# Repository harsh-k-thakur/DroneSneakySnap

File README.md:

# DroneSneakySnap

This project was build as a part of my quarter studies at University of California San Diego.
This project was executed in a group of two. My partner Rye Gleason and I shared the idea and code together to build an end product. 

This project started with understanding dynamics and kinematics of drone. How does Roll, Pitch, Yaw and Throttle works in an open space.

Once I understood the basic dynamics of the drone. 

I started building with the Hardware. For this I used '''Fusion360''' to create new libraries for my IMU, LEDS and Resistors.
Some of the libraries were directly provided to us, and which are readily available in Fusion360 as well. Thus, understanding the basic schematic of a particular part and utilizing the knowledge of that part to integrate in the main project was important. 
You can see datasheet and schmetics of different electronics component under [datasheeet]('/datasheeet/') folder.

All the necessary things related to Hardware are available in [Hardware]('/Hardware/') folder. Things like Schematics, Fusion360 files, Gerber Files are located in the [Hardware]('/Hardware/') folder. Feel free to check those out.

Once done with Hardware, we started working on software. 
While our Printed Circuit Board (PCB) got printed and came back to us we were given a temporary quadcopter in order to start with programming. 
For the software we had Atmega Arduino Micro-controller on the Flight Controller Board. 
Started the project with basic communication between the remote and the quadcopter using Radio Frequency, testing each motors individually works at different spped using Pulse Width Modulation (PWM).
Integrated throttle control from remote and RF together so that we can control the speed using the remote.

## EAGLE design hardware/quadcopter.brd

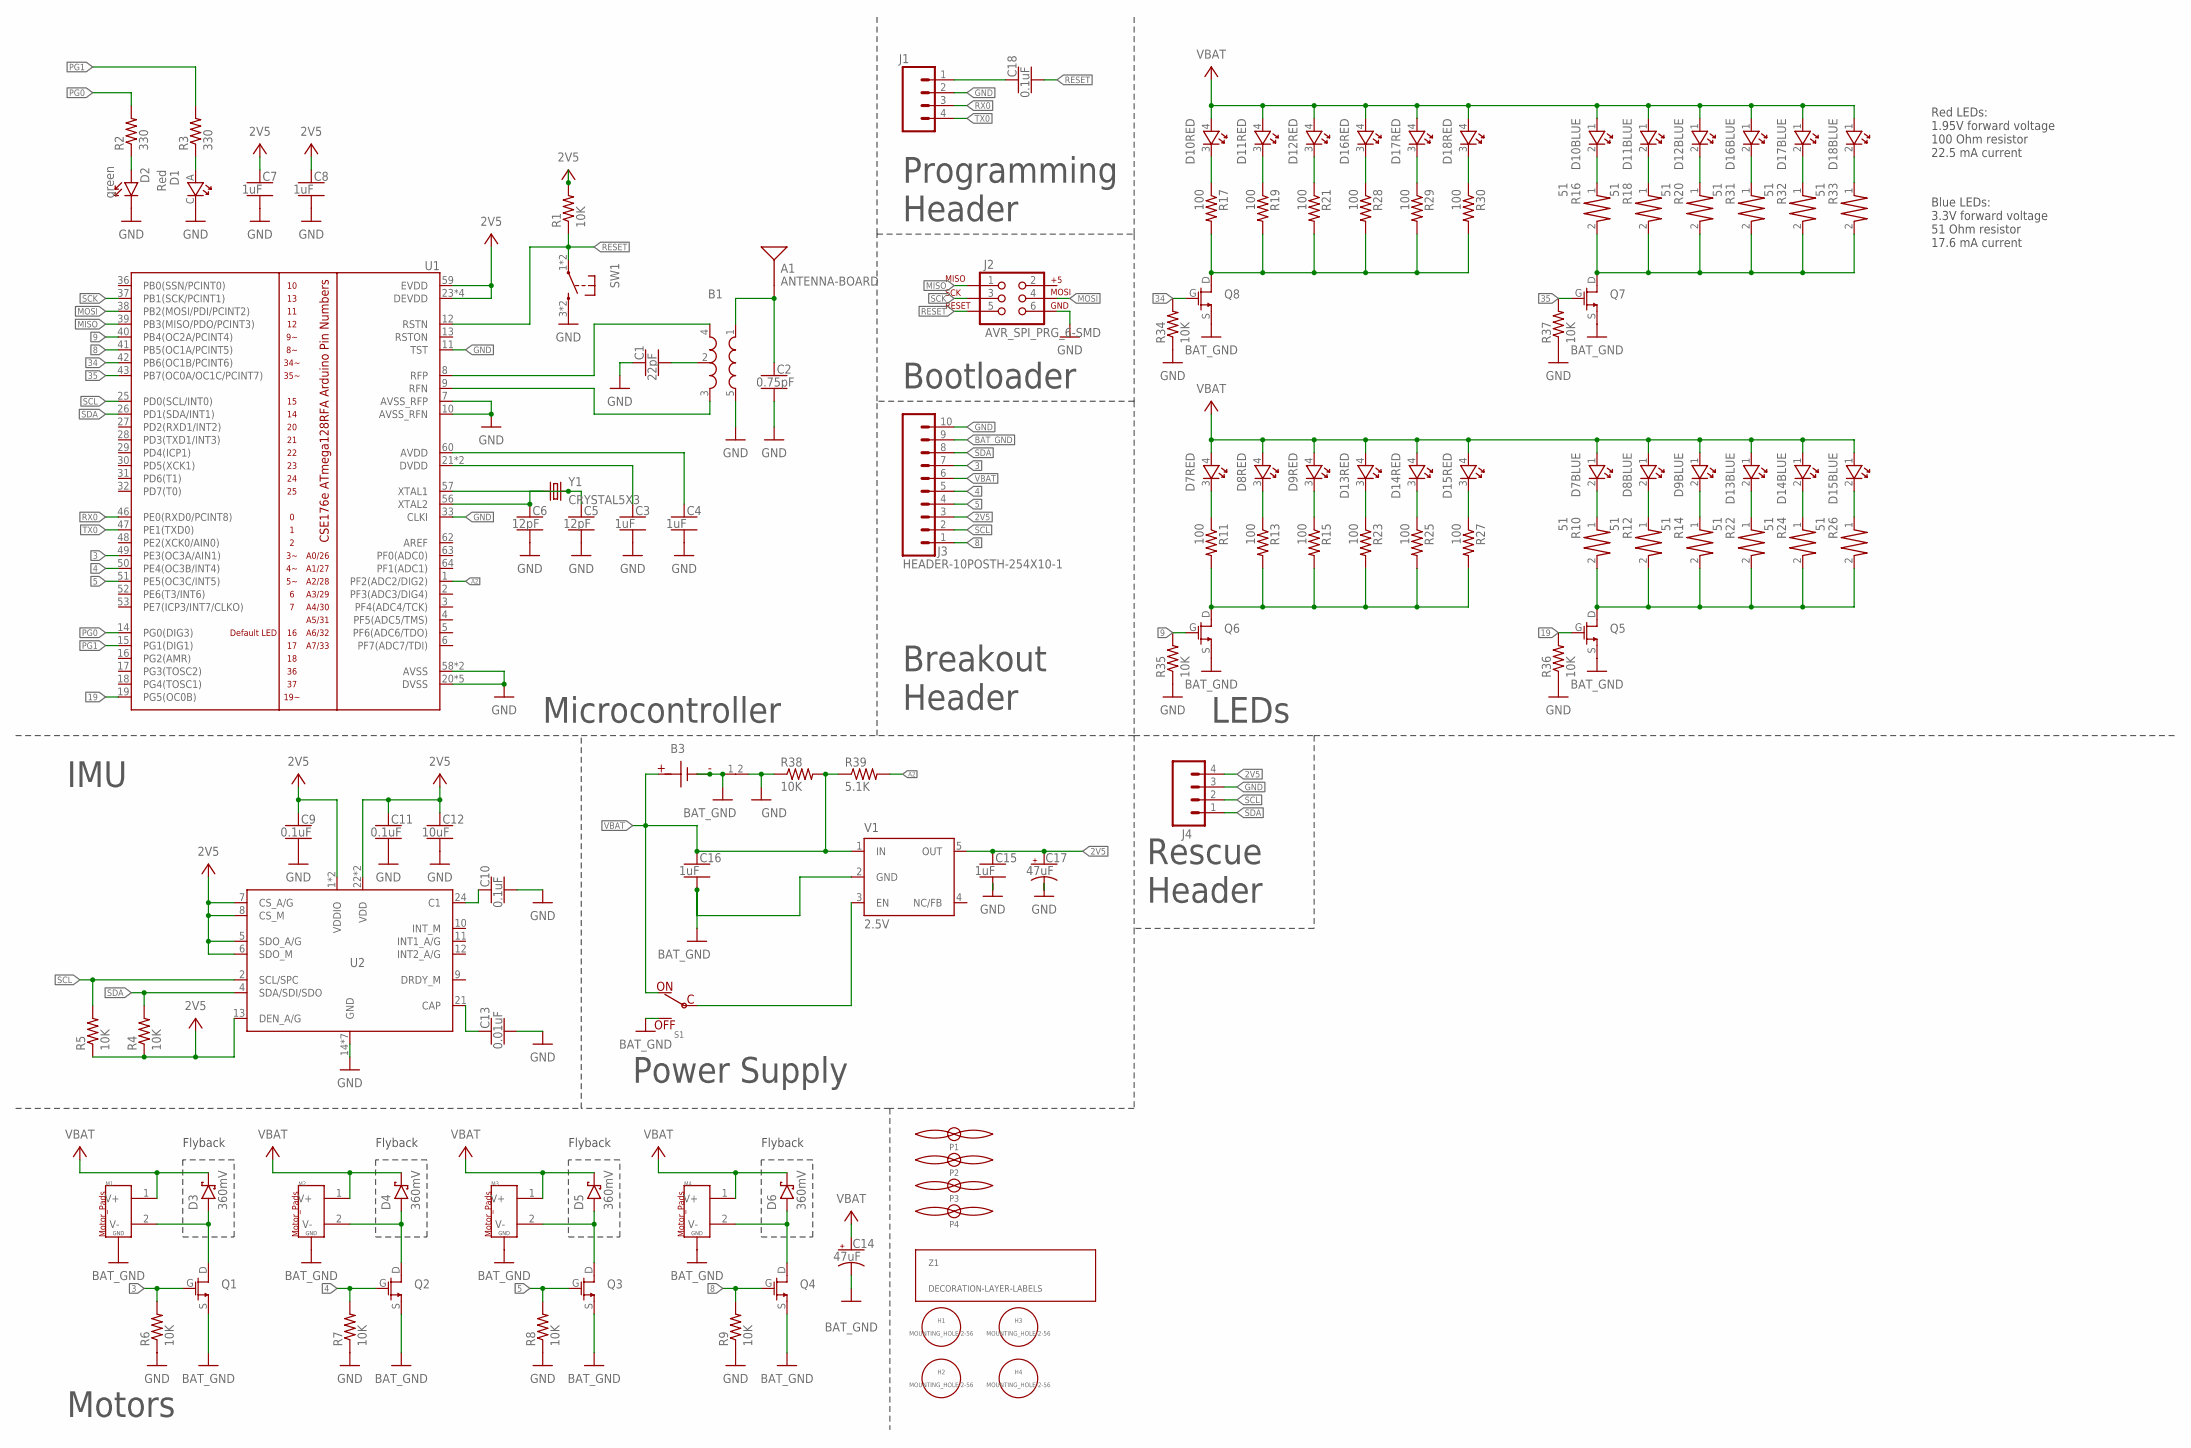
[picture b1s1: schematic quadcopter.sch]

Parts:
A1: ANTENNA-BOARD; ANT_PCB_2.4GHZ_NRF8001_1.6MM_1OZ
B1: BALUN0805; BALUN
B3: BATTERY-SMD-TH; BATTERY-COMBO
C1: 22pF; CAPC2012X140_HS
C2: 0.75pF; CAPC2012X140_HS
C3, C4, C7, C8, C15, C16: 1uF; CAPC2012X140_HS
C5, C6: 12pF; CAPC2012X140_HS
C9, C10, C11, C18: 0.1uF; CAPC2012X140_HS
C12: 10uF; CAPC2012X140_HS
C13: 0.01uF; CAPC2012X140_HS
C14, C17: 47uF; CAPMP3216X180
D1: Red; 0805_LED
D2: green; LEDSC125X200X120-2_HS
D3, D4, D5, D6: 360mV; SODFL3516X96
D7, D8, D9, D10, D11, D12, D13, D14, D15, D16, D17, D18: DUAL_LED0805_RB_LED; 0805_RB_LED
H1, H2, H3, H4: MOUNTING_HOLE-2-56; 2-56-MOUNTING-HOLE-NO-METAL
J1: HEADER-4POS-0.1IN-FEMALE-SMD-BOTTOM-ENTRY; HEADER-1X4-BOTTOM-ENTRY
J2: AVR_SPI_PRG_6-SMD; 2X3-SMD
J3: HEADER-10POSTH-254X10-1; HDRV10W63P254_10X1_2540X254H838_HS
J4: HEADER-4POS-0.1IN-FEMALE; HDRVR4W80P254_1X4_1066X254X850B
M1, M2, M3, M4: MOTOR_PADS_GND-MOLEX-SMD; MOLEX-0532610271
P1, P2, P3, P4: PROPELLOR-45MM; MOTOR_AND_PROP
Q1, Q2, Q3, Q4, Q5, Q6, Q7, Q8: NMOSFETSI2302CDS-T1-E3CT-ND; SOT23_MOSFET
R1, R4, R5, R6, R7, R8, R9, R34, R35, R36, R37, R38: 10K; RESC2012X60_HS
R2, R3: 330; RESC2012X60_HS
R10, R12, R14, R16, R18, R20, R22, R24, R26, R31, R32, R33: 51; 0805_RESISTOR
R11, R13, R15, R17, R19, R21, R23, R25, R27, R28, R29, R30: 100; RESC2012X60_HS
R39: 5.1K; RESC2012X60_HS
S1: POWER-SWITCH-MFS201N-9-Z-SMD-EDGE; JS102011SAQN
SW1: PUSHBUTTON_-4.5X4.5; 4.5MM_TACTILE_SWITCH_TL3305AF160QG
U1: ATMEGA128RFA1; QFN-64
U2: IMU_LSM9DS1LSM9DS1; IMU_LSM9DS1
V1: 2.5V; SOT23-DBV
W1: NET_BRIDGENET_BRIDGE; NET_BRIDGE
Y1: CRYSTAL5X3; CRYSTAL-SMD-5X3
Z1: DECORATION-LAYER-LABELS; LAYER_LABELS

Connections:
2V5: C7.1, C8.1, C9.1, C11.1, C12.1, C15.1, C17.1 (+), J3.3, J4.4, R1.2, R4.1, R5.1, U1.23 (DEVDD), U1.34 (DEVDD), U1.44 (DEVDD), U1.54 (DEVDD), U1.59 (EVDD), U2.1 (VDDIO), U2.3 (VDDIO), U2.5 (SDO_A/G), U2.6 (SDO_M), U2.7 (CS_A/G), U2.8 (CS_M), U2.13 (DEN_A/G), U2.22 (VDD), U2.23 (VDD), V1.5 (OUT)
3: J3.7, Q1.G, R6.2, U1.49 (PE3(OC3A/AIN1))
4: J3.5, Q2.G, R7.2, U1.50 (PE4(OC3B/INT4))
5: J3.4, Q3.G, R8.2, U1.51 (PE5(OC3C/INT5))
8: J3.1, Q4.G, R9.2, U1.41 (PB5(OC1A/PCINT5))
9: Q6.G, R35.2, U1.40 (PB4(OC2A/PCINT4))
19: Q5.G, R36.2, U1.19 (PG5(OC0B))
34: Q8.G, R34.2, U1.42 (PB6(OC1B/PCINT6))
35: Q7.G, R37.2, U1.43 (PB7(OC0A/OC1C/PCINT7))
A2: R39.2, U1.1 (PF2(ADC2/DIG2))
ADRV: A1.FEED, B1.1 (IN), C2.1
BAT_GND: B3.2 (N), B3.G (N), B3.G2 (N), B3.G3 (N), C14.2 (-), C16.2, J3.9, M1.G1 (GND), M1.G2 (GND), M2.G1 (GND), M2.G2 (GND), M3.G1 (GND), M3.G2 (GND), M4.G1 (GND), M4.G2 (GND), Q1.S, Q2.S, Q3.S, Q4.S, Q5.S, Q6.S, Q7.S, Q8.S, S1.A (OFF), V1.2 (GND), W1.1 (PAD_1)
GND: B1.5 (GND), C1.1, C2.2, C3.2, C4.2, C5.2, C6.2, C7.2, C8.2, C9.2, C10.2, C11.2, C12.2, C13.2, C15.2, C17.2 (-), D1.C, D2.C, J1.2, J2.6, J3.10, J4.3, R6.1, R7.1, R8.1, R9.1, R34.1, R35.1, R36.1, R37.1, R38.1, SW1.3 (2), SW1.4 (2), U1.7 (AVSS_RFP), U1.10 (AVSS_RFN), U1.11 (TST), U1.20 (DVSS), U1.24 (DVSS), U1.33 (CLKI), U1.35 (DVSS), U1.45 (DVSS), U1.55 (DVSS), U1.58 (AVSS), U1.61 (AVSS), U2.14 (GND), U2.15 (GND), U2.16 (GND), U2.17 (GND), U2.18 (GND), U2.19 (GND), U2.20 (GND), W1.2 (PAD_2)
MISO: J2.1, U1.39 (PB3(MISO/PDO/PCINT3))
MOSI: J2.4, U1.38 (PB2(MOSI/PDI/PCINT2))
unnamed: S1.C, V1.3 (EN)
unnamed: B1.2 (GND), C1.2
unnamed: C4.1, U1.60 (AVDD)
unnamed: C3.1, U1.21 (DVDD), U1.22 (DVDD)
unnamed: C5.1, U1.57 (XTAL1), Y1.3 (2)
unnamed: C6.1, U1.56 (XTAL2), Y1.1
unnamed: D2.A, R2.1
unnamed: D1.A, R3.1
unnamed: D3.2 (A), M1.2 (V-), Q1.D
unnamed: C10.1, U2.24 (C1)
unnamed: D4.2 (A), M2.2 (V-), Q2.D
unnamed: C13.1, U2.21 (CAP)
unnamed: D5.2 (A), M3.2 (V-), Q3.D
unnamed: D6.2 (A), M4.2 (V-), Q4.D
unnamed: D10.3 (C), R17.1
unnamed: D7.3 (C), R11.1
unnamed: Q8.D, R17.2, R19.2, R21.2, R28.2, R29.2, R30.2
unnamed: Q5.D, R10.2, R12.2, R14.2, R22.2, R24.2, R26.2
unnamed: D7.2 (C), R10.1
unnamed: Q6.D, R11.2, R13.2, R15.2, R23.2, R25.2, R27.2
unnamed: Q7.D, R16.2, R18.2, R20.2, R31.2, R32.2, R33.2
unnamed: D8.3 (C), R13.1
unnamed: C18.1, J1.1
unnamed: D8.2 (C), R12.1
unnamed: D13.3 (C), R23.1
unnamed: D9.3 (C), R15.1
unnamed: D10.2 (C), R16.1
unnamed: D9.2 (C), R14.1
unnamed: D13.2 (C), R22.1
unnamed: D14.3 (C), R25.1
unnamed: D11.3 (C), R19.1
unnamed: D11.2 (C), R18.1
unnamed: D12.3 (C), R21.1
unnamed: D12.2 (C), R20.1
unnamed: D14.2 (C), R24.1
unnamed: D15.3 (C), R27.1
unnamed: D15.2 (C), R26.1
unnamed: D16.3 (C), R28.1
unnamed: D17.3 (C), R29.1
unnamed: D18.3 (C), R30.1
unnamed: D16.2 (C), R31.1
unnamed: D17.2 (C), R32.1
unnamed: D18.2 (C), R33.1
PG0: R2.2, U1.14 (PG0(DIG3))
PG1: R3.2, U1.15 (PG1(DIG1))
RESET: C18.2, J2.5, R1.1, SW1.1, SW1.2 (1), U1.12 (RSTN)
RF_N: B1.3 (OUT2), U1.9 (RFN)
RF_P: B1.4 (OUT1), U1.8 (RFP)
RX0: J1.3, U1.46 (PE0(RXD0/PCINT8))
SCK: J2.3, U1.37 (PB1(SCK/PCINT1))
SCL: J3.2, J4.2, R5.2, U1.25 (PD0(SCL/INT0)), U2.2 (SCL/SPC)
SDA: J3.8, J4.1, R4.2, U1.26 (PD1(SDA/INT1)), U2.4 (SDA/SDI/SDO)
TX0: J1.4, U1.47 (PE1(TXD0))
VBAT: B3.1, B3.P, C14.1 (+), C16.1, D3.1 (C), D4.1 (C), D5.1 (C), D6.1 (C), D7.1 (A), D7.4 (A), D8.1 (A), D8.4 (A), D9.1 (A), D9.4 (A), D10.1 (A), D10.4 (A), D11.1 (A), D11.4 (A), D12.1 (A), D12.4 (A), D13.1 (A), D13.4 (A), D14.1 (A), D14.4 (A), D15.1 (A), D15.4 (A), D16.1 (A), D16.4 (A), D17.1 (A), D17.4 (A), D18.1 (A), D18.4 (A), J3.6, M1.1 (V+), M2.1 (V+), M3.1 (V+), M4.1 (V+), R38.2, R39.1, S1.B (ON), V1.1 (IN)

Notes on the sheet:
Microcontroller
Programming Header
IMU
Bootloader
Flyback
Breakout Header
Power Supply
Motors
LEDs
Red LEDs: 1.95V forward voltage 100 Ohm resistor 22.5 mA current
Blue LEDs: 3.3V forward voltage 51 Ohm resistor 17.6 mA current
Rescue Header

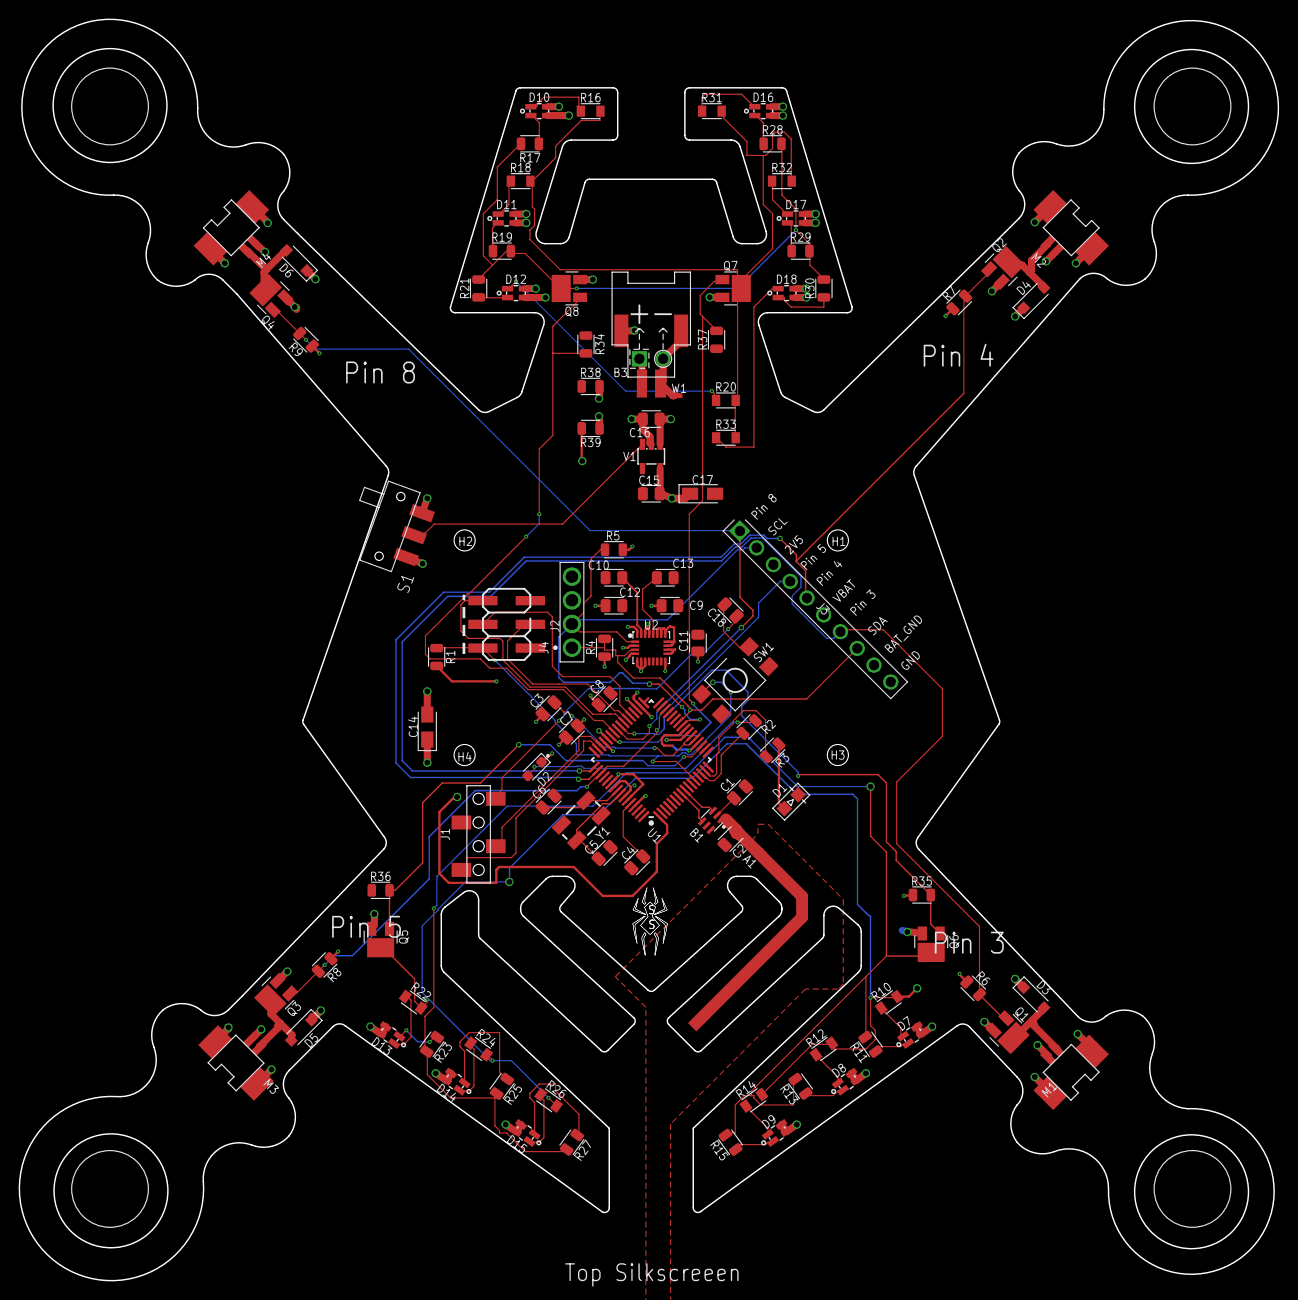
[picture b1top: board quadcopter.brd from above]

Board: 4 copper layers, 134.9 x 135.2 mm, 112 parts (0 on the bottom side), 69 nets.

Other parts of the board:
L1, L2: DECORATIONSNEAKYSNAP; SNEAKYSNAP_LOGO

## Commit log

2022-03-28 Firmware
2022-03-28 Hardware
2022-03-28 Datasheet
2022-03-28 Eagle Files
2022-03-28 Labs
